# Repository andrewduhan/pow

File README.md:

POW!
====

CMOY-style headphone amp with adjustable boost supply and battery management

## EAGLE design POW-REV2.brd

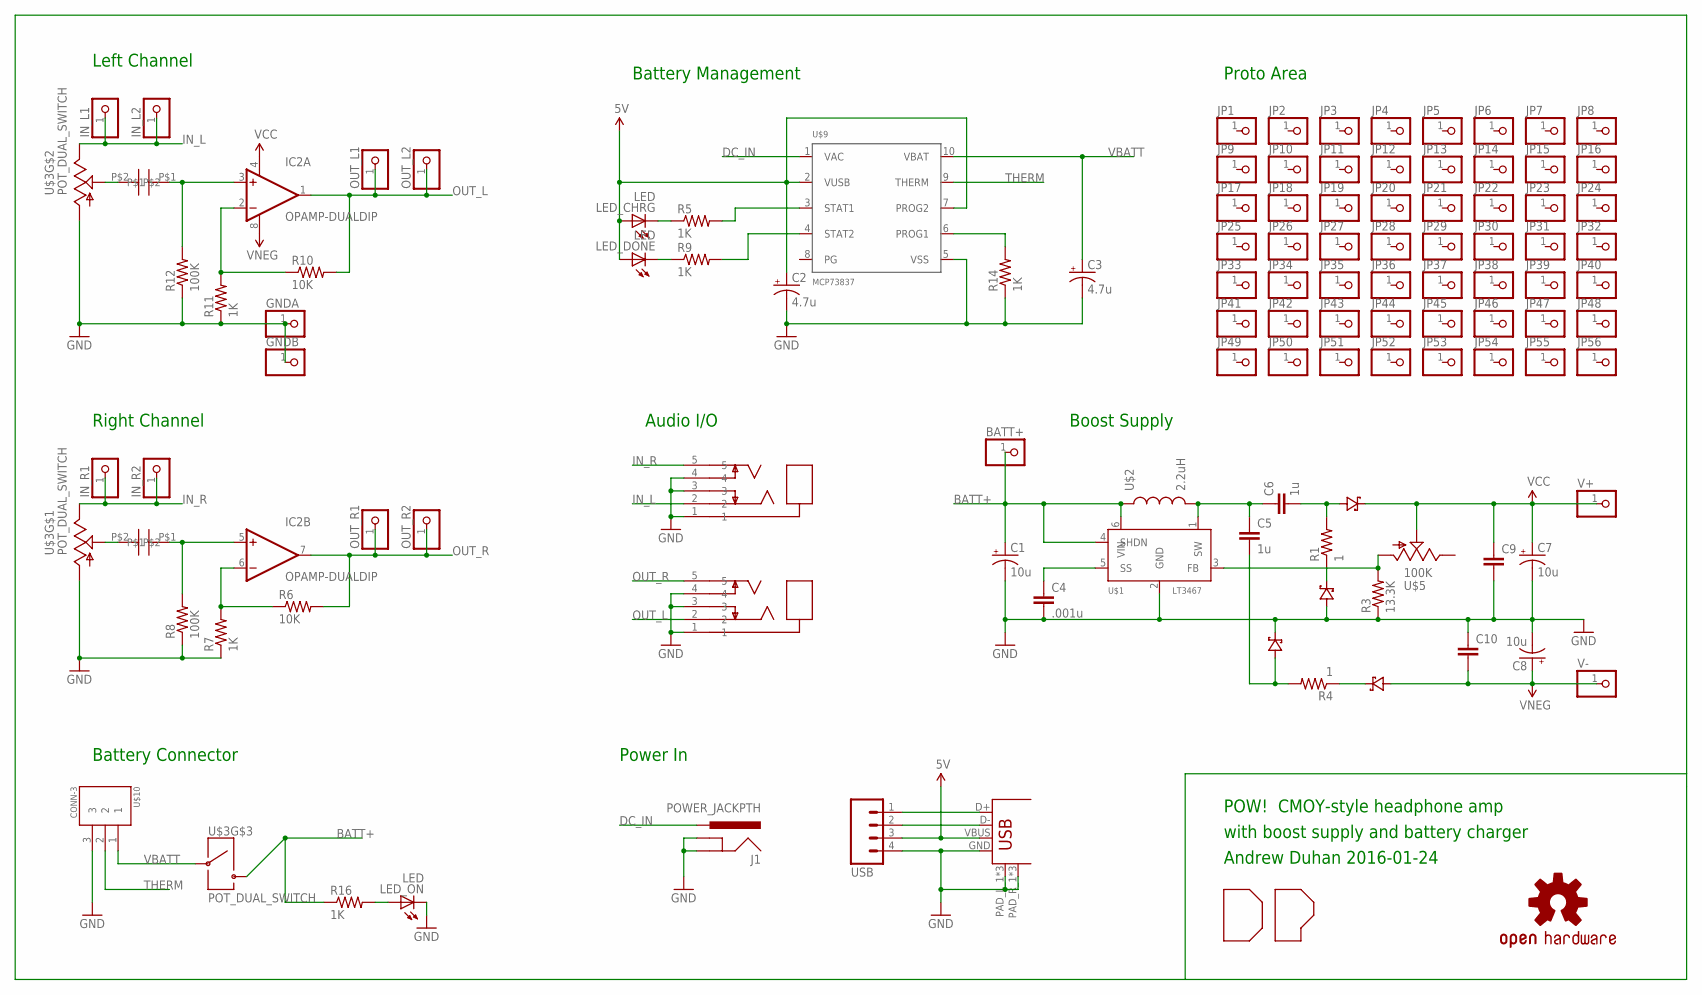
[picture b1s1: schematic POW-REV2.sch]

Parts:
BATT+: PINHD-1X1CB; 1X01-CLEANBIG
C1, C7, C8: 10u; E2,5-6E
C2, C3: 4.7u; E2,5-6E
C4: .001u; CAP-PTH-SMALL
C5, C6: 1u; CAP-PTH-SMALL
C9, C10: CAPPTH; CAP-PTH-SMALL
D2, D5, D6, D7: SCHOTTKY; SOD-123
GNDA: PINHD-1X1CB; 1X01-CLEANBIG
GNDB: PINHD-1X1CB; 1X01-CLEANBIG
IC2: OPAMP-DUALDIP; DIP08
IN_JACK: JACK_STEREO_SWCUI-SJ1-351X; AUDIO_JACK-CUI-SJ1-351X
IN_L1, IN_L2: PINHD-1X1CB; 1X01-CLEANBIG
IN_R1, IN_R2: PINHD-1X1CB; 1X01-CLEANBIG
J1: POWER_JACKPTH; POWER_JACK_PTH
JP1, JP2, JP3, JP4, JP5, JP6, JP7, JP8, JP9, JP10, JP11, JP12, JP13, JP14, JP15, JP16, JP17, JP18, JP19, JP20, JP21, JP22, JP23, JP24, JP25, JP26, JP27, JP28, JP29, JP30, JP31, JP32, JP33, JP34, JP35, JP36, JP37, JP38, JP39, JP40, JP41, JP42, JP43, JP44, JP45, JP46, JP47, JP48, JP49, JP50, JP51, JP52, JP53, JP54, JP55, JP56: PINHD-1X1CB; 1X01-CLEANBIG
LED_CHRG: LED; SSF-LXH25780ID
LED_DONE: LED; SSF-LXH25780ID
LED_ON: LED; SSF-LXH25780ID
LOGO1: OSHW-LOGOS; OSHW-LOGO-S
OUT_JACK: JACK_STEREO_SWCUI-SJ1-351X; AUDIO_JACK-CUI-SJ1-351X
OUT_L1, OUT_L2: PINHD-1X1CB; 1X01-CLEANBIG
OUT_R1, OUT_R2: PINHD-1X1CB; 1X01-CLEANBIG
R1, R4: 1; AXIAL-0.3
R3: 13.3K; AXIAL-0.3
R5, R7, R9, R11, R14, R16: 1K; AXIAL-0.3
R6, R10: 10K; AXIAL-0.3
R8, R12: 100K; AXIAL-0.3
U$1: LT3467; SOT23-6
U$2: 2.2uH; INDUCTOR_4.5X5
U$3: POT_DUAL_SWITCH; POT_ALPS_RK097
U$4: USB; USB-MICRO-MOLEX-SMD
U$5: 100K; TRIM-MURATA-PV36W
U$6: DP_LOGO
U$7, U$8: 0.1u; CAP-MKP_RADIAL
U$9: MCP73837; MSOP-10
U$10: CONN-3; CONN-0530480310
USB: M04PTH; 1X04
V+: PINHD-1X1CB; 1X01-CLEANBIG
V-: PINHD-1X1CB; 1X01-CLEANBIG

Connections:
5V: C2.+, LED_CHRG.ANODE (A), LED_DONE.ANODE (A), U$4.VBUS, U$9.2 (VUSB), U$9.7 (PROG2), USB.3
BATT+: BATT+.1, C1.+, R16.P$1 (1), U$1.4 (SHDN), U$1.6 (VIN), U$2.P$1 (1), U$3.SW1 (1)
DC_IN: J1.PWR, U$9.1 (VAC)
GND: C1.-, C2.-, C3.-, C4.2, C7.-, C8.-, C9.2, C10.1, D5.ANODE, D6.CATHODE, GNDA.1, GNDB.1, IN_JACK.1, IN_JACK.3, IN_JACK.4, J1.GND, J1.GNDBREAK, LED_ON.CATHODE (C), OUT_JACK.1, OUT_JACK.3, OUT_JACK.4, R3.P$1 (1), R7.P$1 (1), R8.P$1 (1), R11.P$1 (1), R12.P$1 (1), R14.P$1 (1), U$1.2 (GND), U$3.POT1_A (A), U$3.POT2_A (A), U$4.GND, U$4.PAD_L_1, U$4.PAD_L_2, U$4.PAD_L_3, U$4.PAD_R_1, U$4.PAD_R_2, U$4.PAD_R_3, U$9.5 (VSS), U$10.3, USB.4
IN_L: IN_JACK.2, IN_L1.1, IN_L2.1, U$3.POT2_B (B)
IN_R: IN_JACK.5, IN_R1.1, IN_R2.1, U$3.POT1_B (B)
unnamed: LED_ON.ANODE (A), R16.P$2 (2)
unnamed: LED_CHRG.CATHODE (C), R5.P$1 (1)
unnamed: C4.1, U$1.5 (SS)
unnamed: C5.1, C6.1, U$1.1 (SW), U$2.P$2 (2)
unnamed: C5.2, D6.ANODE, R4.P$2 (2)
unnamed: R3.P$2 (2), U$1.3 (FB), U$5.A
unnamed: C6.2, D7.ANODE, R1.P$2 (2)
unnamed: IC2.6 (-IN), R6.P$1 (1), R7.P$2 (2)
unnamed: D2.CATHODE, R4.P$1 (1)
unnamed: IC2.5 (+IN), R8.P$2 (2), U$7.P$1
unnamed: D5.CATHODE, R1.P$1 (1)
unnamed: IC2.3 (+IN), R12.P$2 (2), U$8.P$1
unnamed: IC2.2 (-IN), R10.P$1 (1), R11.P$2 (2)
unnamed: LED_DONE.CATHODE (C), R9.P$1 (1)
unnamed: U$3.POT1_W (W), U$7.P$2
unnamed: U$3.POT2_W (W), U$8.P$2
unnamed: R5.P$2 (2), U$9.3 (STAT1)
unnamed: R9.P$2 (2), U$9.4 (STAT2)
unnamed: R14.P$2 (2), U$9.6 (PROG1)
OUT_L: IC2.1 (OUT), OUT_JACK.2, OUT_L1.1, OUT_L2.1, R10.P$2 (2)
OUT_R: IC2.7 (OUT), OUT_JACK.5, OUT_R1.1, OUT_R2.1, R6.P$2 (2)
THERM: U$9.9 (THERM), U$10.2
USB_D+: U$4.D+, USB.1
USB_D-: U$4.D-, USB.2
VBATT: C3.+, U$3.SW2 (2), U$9.10 (VBAT), U$10.1
VCC: C7.+, C9.1, D7.CATHODE, IC2.4 (V-), U$5.W, V+.1
VNEG: C8.+, C10.2, D2.ANODE, IC2.8 (V+), V-.1

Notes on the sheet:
Left Channel
Right Channel
Battery Connector
Boost Supply
Proto Area
Battery Management
Audio I/O
Power In
POW! CMOY-style headphone amp
with boost supply and battery charger
Andrew Duhan 2016-01-24

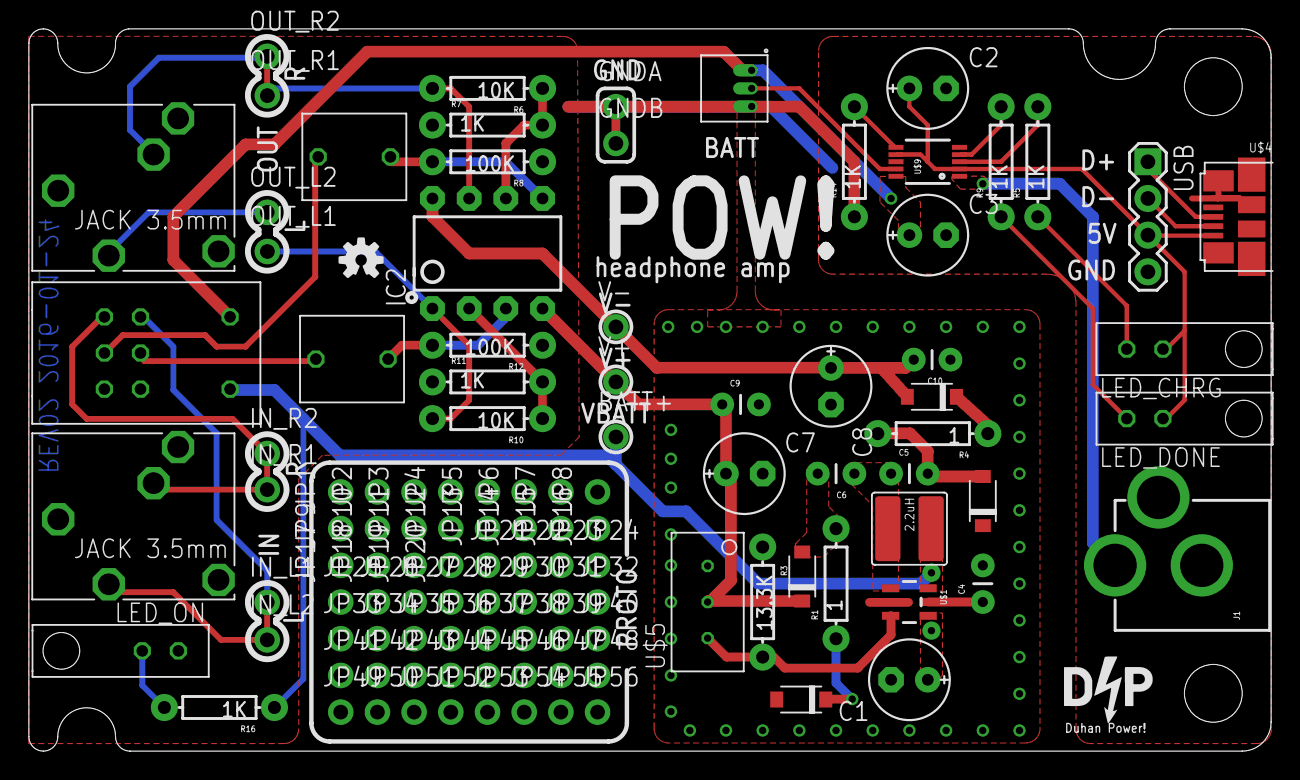
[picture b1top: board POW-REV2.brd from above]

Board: 2 copper layers, 86.0 x 50.0 mm, 115 parts (0 on the bottom side), 33 nets.

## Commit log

2016-01-25 add pdf schematic
2016-01-25 DXF board outline

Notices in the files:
parts and their libraries:
SparkFun-Capacitors: Licensing: CC v3.0 Share-Alike You are welcome to use this library for commercial purposes.
